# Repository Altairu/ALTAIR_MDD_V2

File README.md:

# ALTAIR_MDD_V2
ALTAIR_MDD_V2

> encoder
 * A0 A1
 * B3 A5
 * B6 B7
 * C5 C7

> MD
 * B14 B15
 * A8 A11
 * A6 A7
 * B8 B9

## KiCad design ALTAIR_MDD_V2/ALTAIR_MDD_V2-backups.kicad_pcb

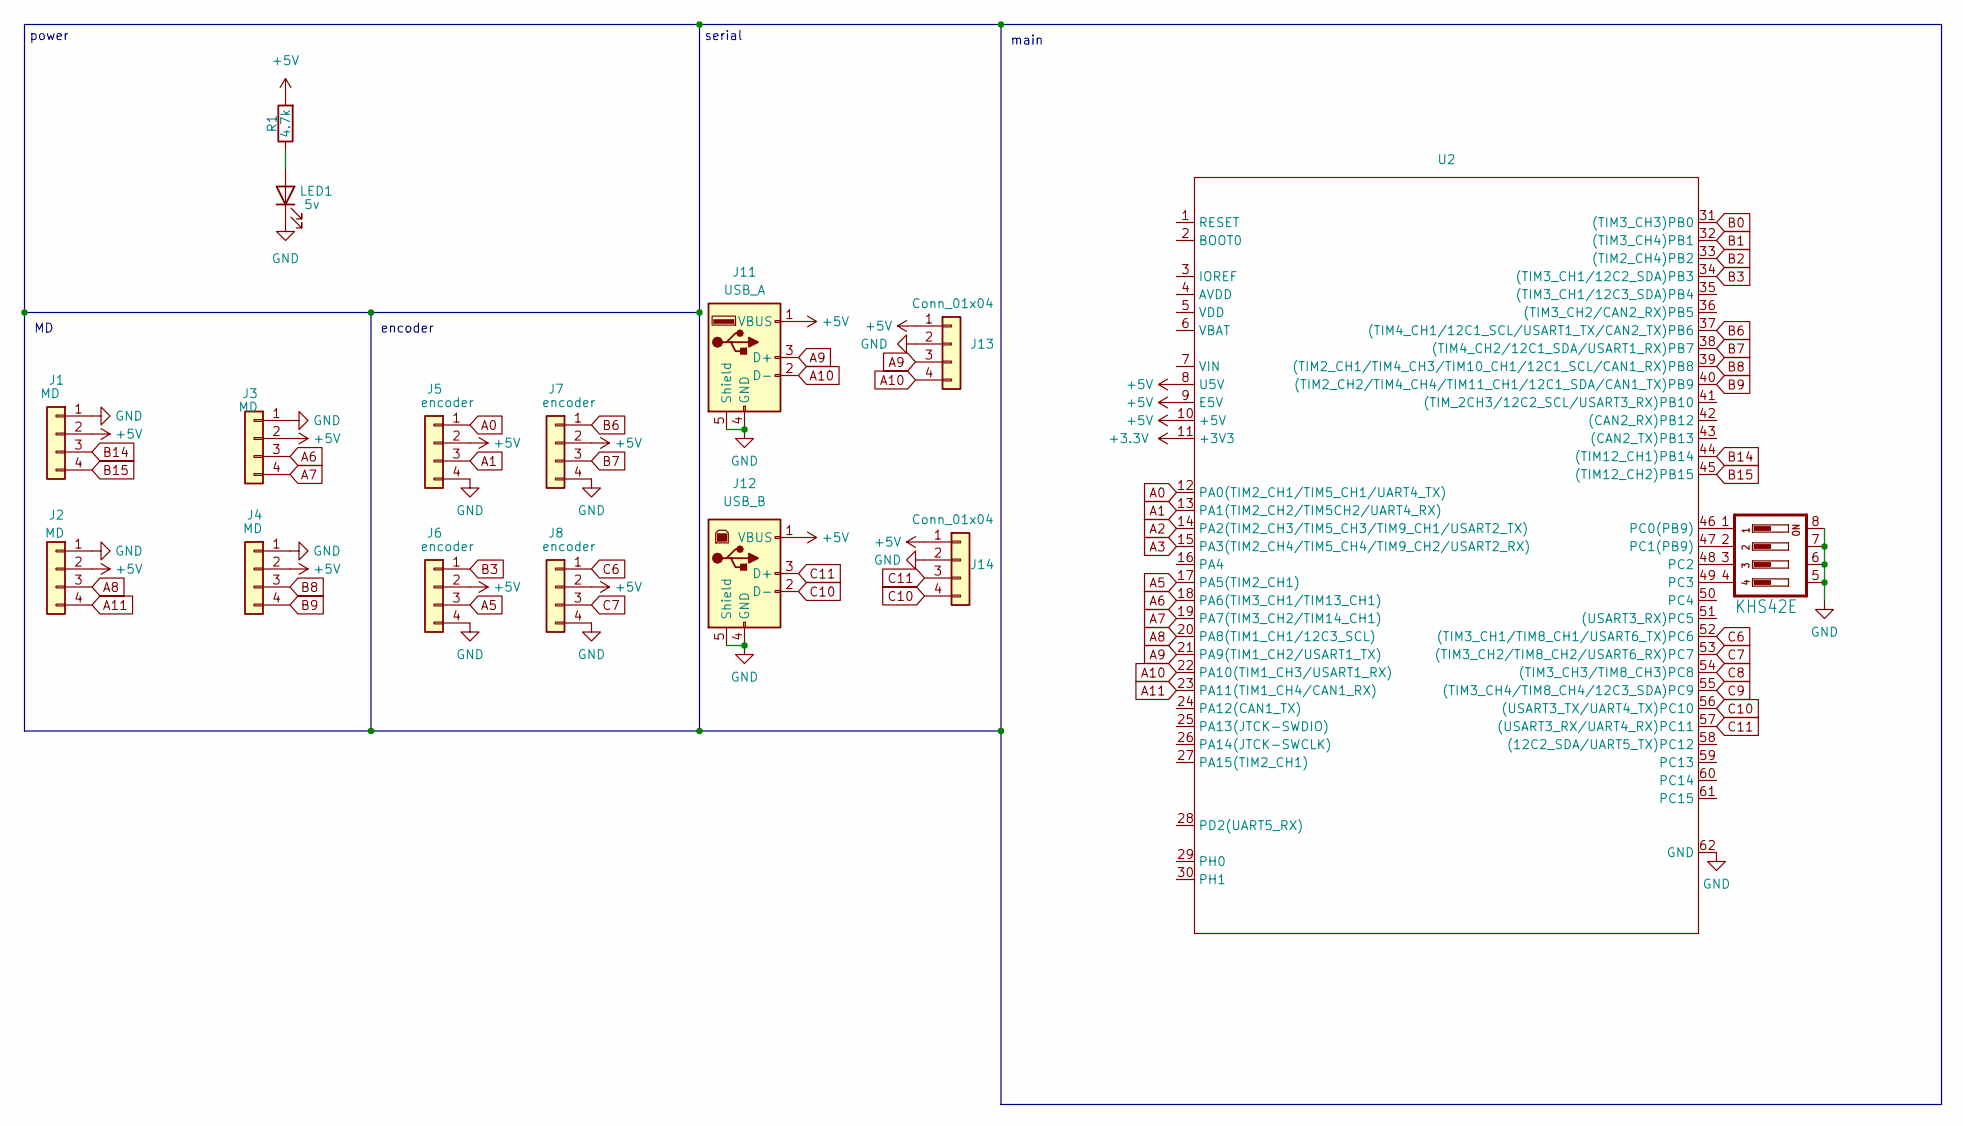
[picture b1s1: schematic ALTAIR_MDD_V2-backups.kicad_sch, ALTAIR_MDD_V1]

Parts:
J1, J2, J3, J4: MD; JST_XA_S04B-XASK-1_1x04_P2.50mm_Horizontal
J5, J6, J7, J8: encoder; JST_XA_S04B-XASK-1_1x04_P2.50mm_Horizontal
J11: USB_A; USB_A_Molex_67643_Horizontal
J12: USB_B; USB_B_Lumberg_2411_02_Horizontal
J13, J14: Conn_01x04; JST_XA_B04B-XASK-1_1x04_P2.50mm_Vertical
LED1: 5v; LED_0603_1608Metric
R1: 4.7k; R_0603_1608Metric
S2: KHS42E; SOIC127P600X175-8N
U2: STM32F446RE_Nucleo

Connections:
+3.3V: U2.11 (+3V3)
+5V: J1.2, J2.2, J3.2, J4.2, J5.2, J6.2, J7.2, J8.2, J11.1 (VBUS), J12.1 (VBUS), J13.1, J14.1, R1.2, U2.8 (U5V), U2.9 (E5V), U2.10 (+5V)
A0: J5.1, U2.12 (PA0(TIM2_CH1/TIM5_CH1/UART4_TX))
A1: J5.3, U2.13 (PA1(TIM2_CH2/TIM5CH2/UART4_RX))
A2: U2.14 (PA2(TIM2_CH3/TIM5_CH3/TIM9_CH1/USART2_T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)
A3: U2.15 (PA3(TIM2_CH4/TIM5_CH4/TIM9_CH2/USART2_R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)
A5: J6.3, U2.17 (PA5(TIM2_CH1))
A6: J3.3, U2.18 (PA6(TIM3_CH1/TIM13_CH1))
A7: J3.4, U2.19 (PA7(TIM3_CH2/TIM14_CH1))
A8: J2.3, U2.20 (PA8(TIM1_CH1/12C3_SCL))
A9: J11.3 (D+), J13.3, U2.21 (PA9(TIM1_CH2/USART1_TX))
A10: J11.2 (D-), J13.4, U2.22 (PA10(TIM1_CH3/USART1_RX))
A11: J2.4, U2.23 (PA11(TIM1_CH4/CAN1_RX))
B0: U2.31 ((TIM3_CH3)PB0)
B1: U2.32 ((TIM3_CH4)PB1)
B2: U2.33 ((TIM2_CH4)PB2)
B3: J6.1, U2.34 ((TIM3_CH1/12C2_SDA)PB3)
B6: J7.1, U2.37 ((TIM4_CH1/12C1_SCL/USART1_TX/CAN2_TX)PB6)
B7: J7.3, U2.38 ((TIM4_CH2/12C1_SDA/USART1_RX)PB7)
B8: J4.3, U2.39 ((TIM2_CH1/TIM4_CH3/TIM10_CH1/12C1_SCL/C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)
B9: J4.4, U2.40 ((TIM2_CH2/TIM4_CH4/TIM11_CH1/12C1_SDA/C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)
B14: J1.3, U2.44 ((TIM12_CH1)PB14)
B15: J1.4, U2.45 ((TIM12_CH2)PB15)
C6: J8.1, U2.52 ((TIM3_CH1/TIM8_CH1/USART6_TX)PC6)
C7: J8.3, U2.53 ((TIM3_CH2/TIM8_CH2/USART6_RX)PC7)
C8: U2.54 ((TIM3_CH3/TIM8_CH3)PC8)
C9: U2.55 ((TIM3_CH4/TIM8_CH4/12C3_SDA)PC9)
C10: J12.2 (D-), J14.4, U2.56 ((USART3_TX/UART4_TX)PC10)
C11: J12.3 (D+), J14.3, U2.57 ((USART3_RX/UART4_RX)PC11)
GND: J1.1, J2.1, J3.1, J4.1, J5.4, J6.4, J7.4, J8.4, J11.4 (GND), J11.5 (Shield), J12.4 (GND), J12.5 (Shield), J13.2, J14.2, LED1.1 (K), S2.5, S2.6, S2.7, S2.8, U2.62 (GND)
unnamed: LED1.2 (A), R1.1
unnamed: S2.1, U2.46 (PC0(PB9))
unnamed: S2.2, U2.47 (PC1(PB9))
unnamed: S2.3, U2.48 (PC2)
unnamed: S2.4, U2.49 (PC3)

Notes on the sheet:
serial
encoder
main
power

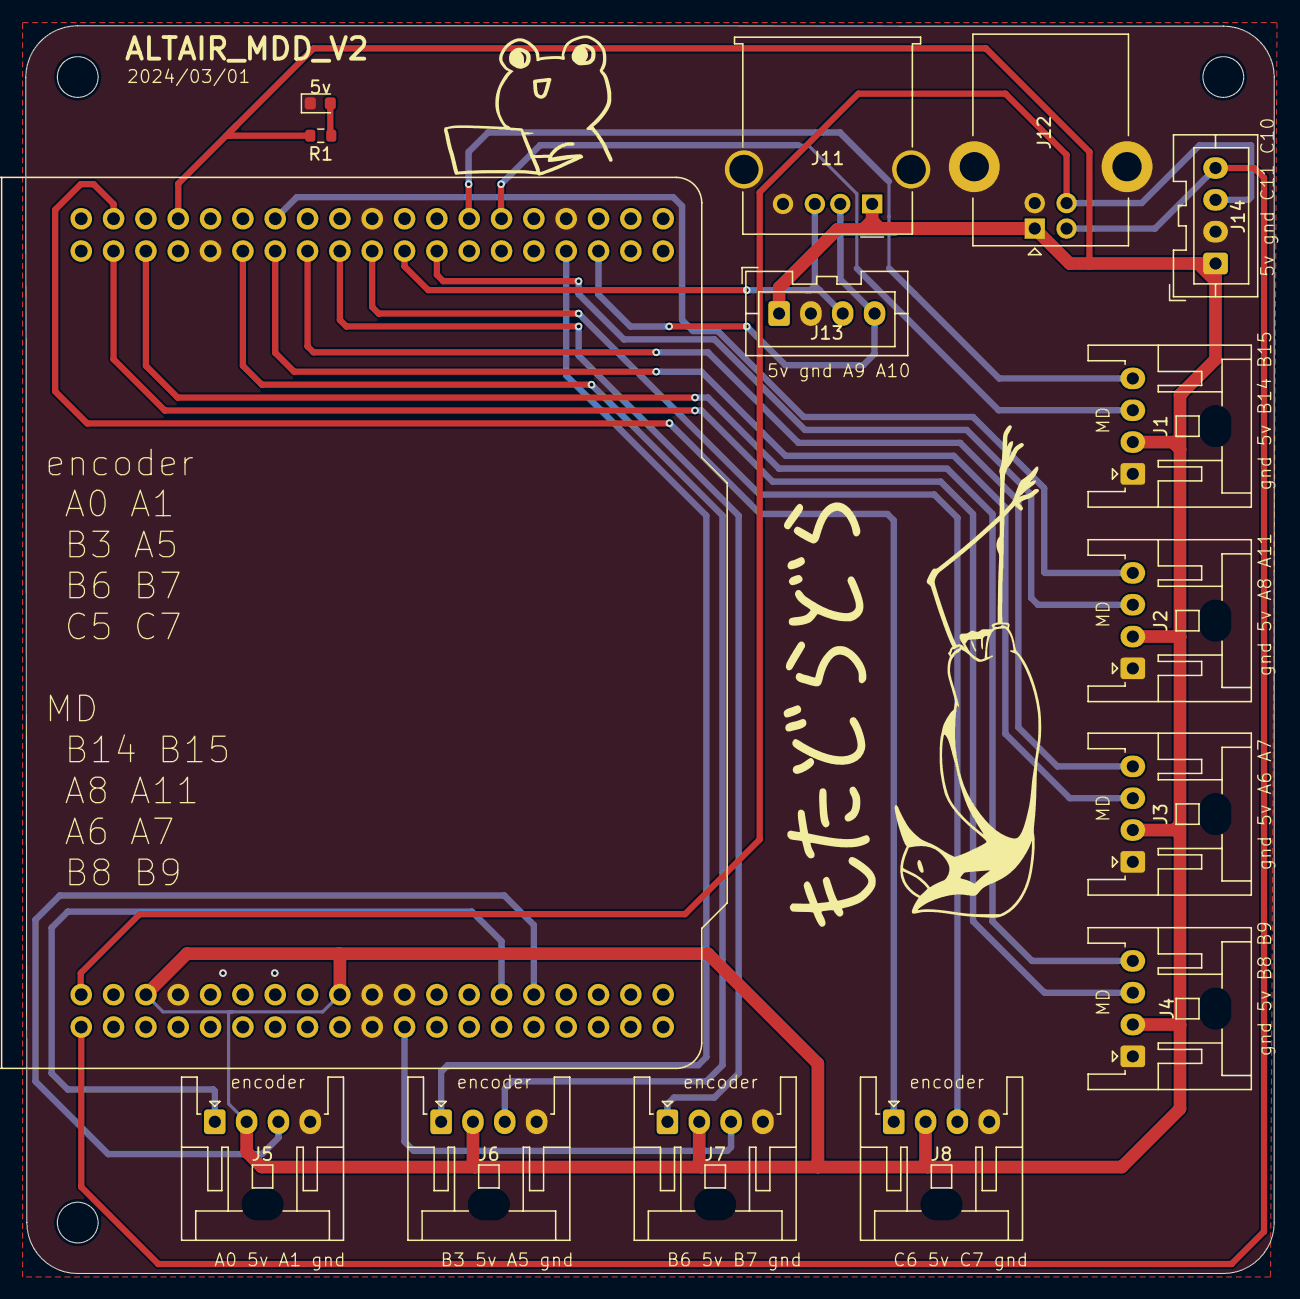
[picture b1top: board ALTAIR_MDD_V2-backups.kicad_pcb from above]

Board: 2 copper layers, 98.1 x 98.0 mm, 15 parts (0 on the bottom side), 23 nets.
